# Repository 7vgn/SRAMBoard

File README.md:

# SRAM Board evolved
## An Add-On for the ATmega644(A) Evaluation Board

This is an add-on for the [EvaBoard evolved](https://github.com/7vgn/EvaBoard/) ATmega644(A) evaluation board. It is inspired by (and compatible with) the [add-on board](https://www.embedded.rwth-aachen.de/doku.php?id=lehre:atmegaevaboard) used in the lab course "Praktikum Systemprogrammierung" in the computer science curriculum at RWTH Aachen. It can be used both with the original evaluation board and its remake. 

This repository contains:

- A richly illustrated [Guide Book](Guide/SRAMBoardGuide.pdf) with everything you need to know to build and use the board
- A [KiCAD project](KiCAD/) with the [Schematic](KiCAD/Schematic.pdf) and a PCB layout, ready to be manufactured
- The [bill of materials](BOM/BOM.pdf)
- [Test code](Tests/) for testing and debugging the board

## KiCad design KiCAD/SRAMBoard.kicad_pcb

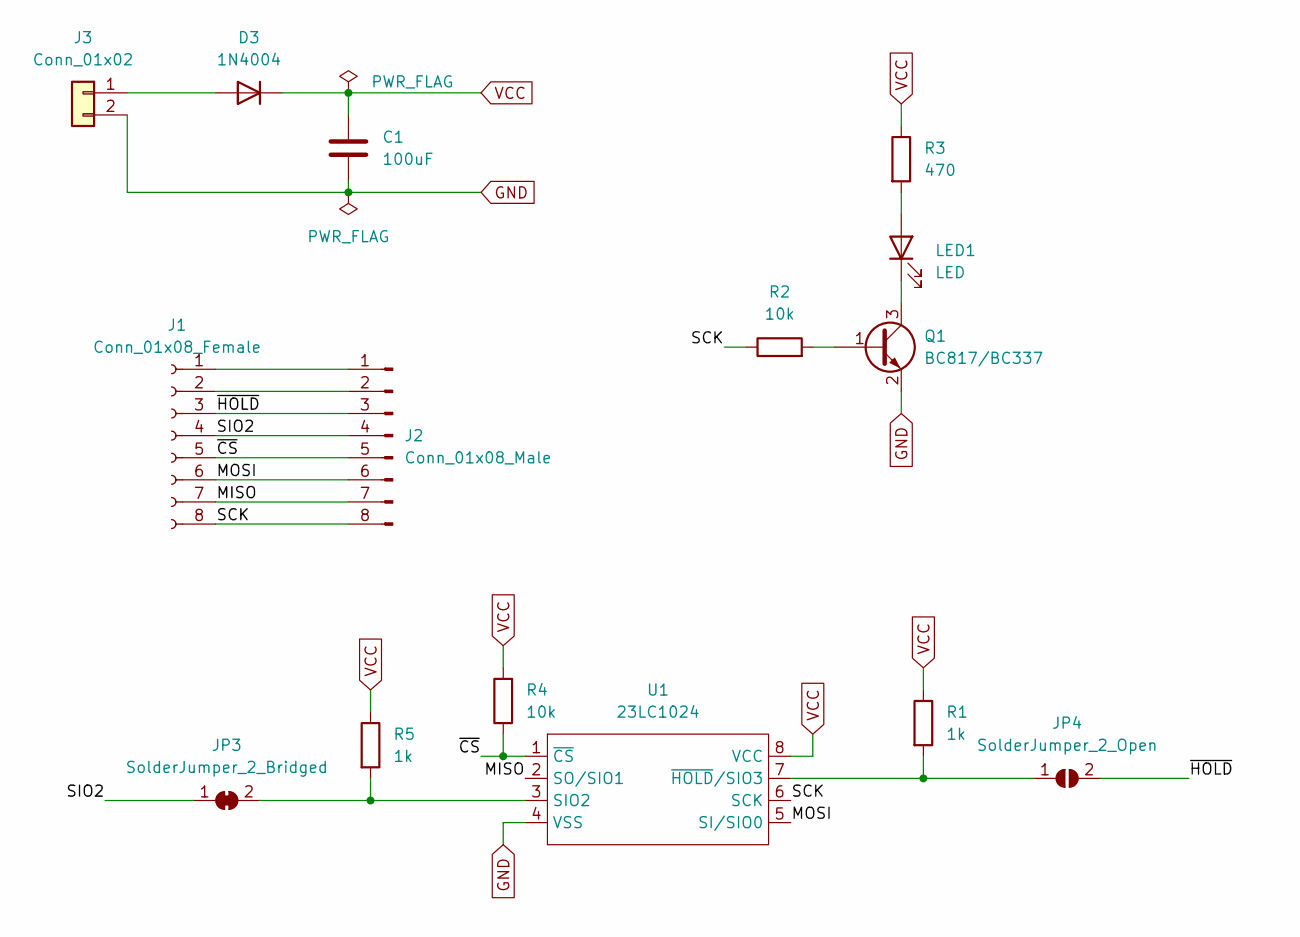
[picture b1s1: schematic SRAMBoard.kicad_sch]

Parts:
C1: 100uF; C_THT10.16mm_SMD1206
D3: 1N4004; D_MELF-RM10_Universal_Handsoldering
J1: Conn_01x08_Female; PinSocket_1x08_P2.54mm_Vertical
J2: Conn_01x08_Male; PinHeader_1x08_P2.54mm_Vertical
J3: Conn_01x02; PinHeader_1x02_P2.54mm_Vertical
JP3: SolderJumper_2_Bridged; SolderJumper-2_P1.3mm_Bridged_RoundedPad1.0x1.5mm
JP4: SolderJumper_2_Open; SolderJumper-2_P1.3mm_Open_RoundedPad1.0x1.5mm
LED1: LED; LED_THT3mm_SMD1206
Q1: BC817/BC337; Q_SOT23_TO92
R1, R5: 1k; R_THT10.16mm_SMD1206
R2, R4: 10k; R_THT10.16mm_SMD1206
R3: 470; R_THT10.16mm_SMD1206
U1: 23LC1024; DIP_SO_8

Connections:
/MISO: J1.7, J2.7, U1.2 (SO/SIO1)
/MOSI: J1.6, J2.6, U1.5 (SI/SIO0)
/SCK: J1.8, J2.8, R2.1, U1.6 (SCK)
/SIO2: J1.4, J2.4, JP3.1 (A)
/~CS: J1.5, J2.5, R4.1, U1.1 (~CS)
/~HOLD: J1.3, J2.3, JP4.2 (B)
GND: C1.2, J3.2, Q1.2 (E), U1.4 (VSS)
unnamed: D3.2 (A), J3.1
unnamed: J1.1, J2.1
unnamed: J1.2, J2.2
unnamed: JP3.2 (B), R5.2, U1.3 (SIO2)
unnamed: JP4.1 (A), R1.2, U1.7 (~HOLD/SIO3)
unnamed: LED1.1 (K), Q1.3 (C)
unnamed: LED1.2 (A), R3.2
unnamed: Q1.1 (B), R2.2
VCC: C1.1, D3.1 (K), R1.1, R3.1, R4.2, R5.1, U1.8 (VCC)

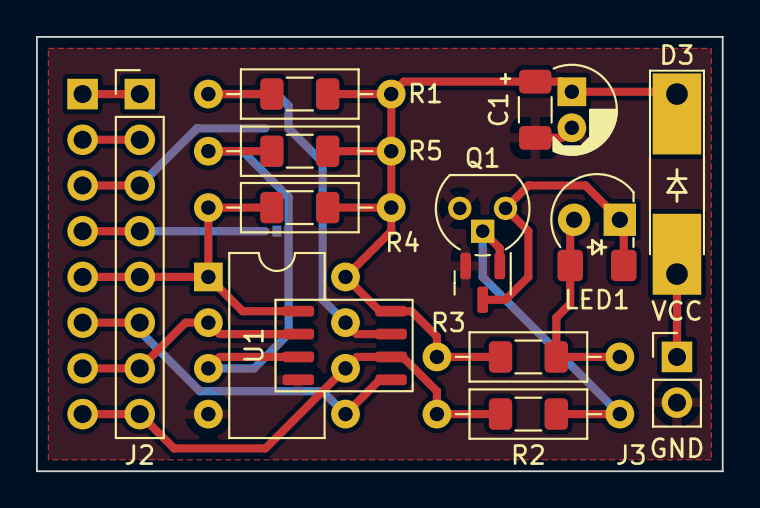
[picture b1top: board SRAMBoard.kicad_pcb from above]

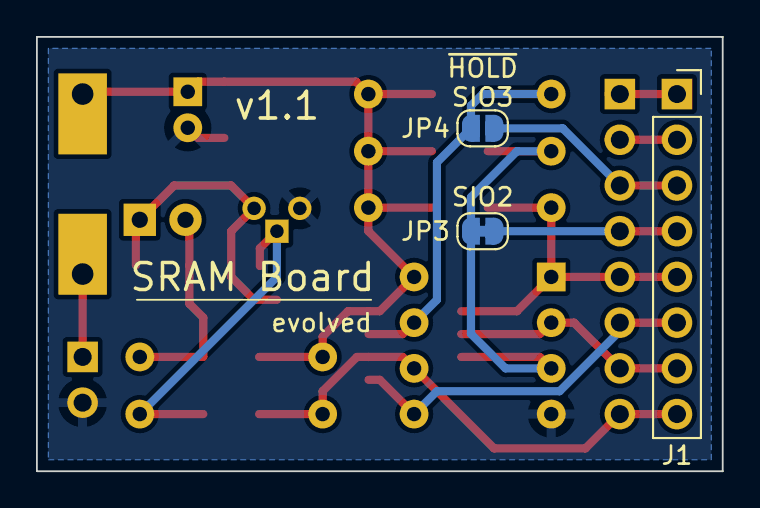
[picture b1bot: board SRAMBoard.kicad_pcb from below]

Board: 2 copper layers, 38.1 x 24.1 mm, 15 parts (3 on the bottom side), 16 nets.

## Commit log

2024-02-29 Removed WIP warning
